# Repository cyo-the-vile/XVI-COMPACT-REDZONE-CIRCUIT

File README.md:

# XVI-COMPACT-REDZONE-CIRCUIT
Simple circuit to overclock XVI Compact

To build this circuit it is recommended you send this board to a manufacturer to make a blank PCB. I prefer JLCPCB.  Both zipped files are what are good to send to a PCB manufacturer.  

The XVI Compact is capable of being clocked up to 24mhz.  After 25mhz the processor will become unstable.

This circuit is based on the one in the Oh! Magazine scans.  Hlide was very nice also also made a circuit with DIP packages.  Anyway this is SMD packaging board so it's smaller.
There are two solder points labeled SW for a switch.
There are 4 solder points labeled for 5V, GND, I AND O.  This is important for soldering wires to the motherboard for overclocking.

Anyway the BOM consists of:

-DIP 14 socket...trim it so it can insert properly. It will fit.  This gives you leverage on what size crystal to use.

-If you want a 24mhz computer you will need a 48mhz oscillator since clock divider is 2.  
For a 20mhz computer you will need 40mhz oscillator. They need to be in DIP package and 5V.

-4.7K OHM resistor specifcally in 0603 SMD package.

-SN74F157AD which is the SOIC16 package.

This will be updated as I build mine and test it live.

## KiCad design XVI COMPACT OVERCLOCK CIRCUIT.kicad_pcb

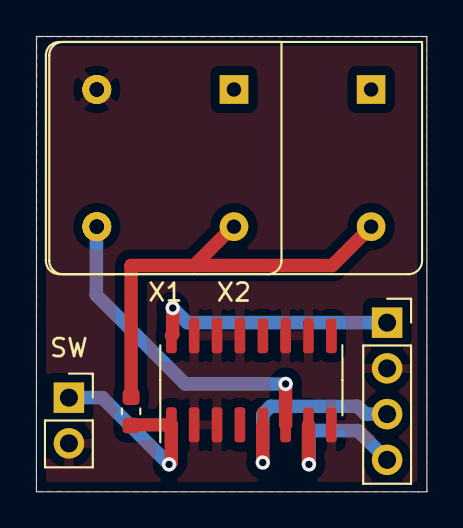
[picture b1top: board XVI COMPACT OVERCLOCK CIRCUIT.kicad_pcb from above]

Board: 2 copper layers, 21.7 x 25.3 mm, 6 parts (0 on the bottom side), 5 nets.

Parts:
J2: Conn_01x04; PinSocket_1x04_P2.54mm_Vertical
R1: 4.7K; R_0603_1608Metric
SW: FOR SWITCH; PinSocket_1x02_P2.54mm_Vertical
U1: SOIC16; SOIC-16_3.9x9.9mm_P1.27mm
X1: CXO_DIP8; Oscillator_DIP-8
X2: CXO_DIP14; Oscillator_DIP-14

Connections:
/GND: J2.2, SW.2, U1.2, U1.3, U1.8, U1.10, U1.11, U1.13, U1.14, U1.15, X1.4, X2.7
/I: J2.3, U1.5
/O: J2.4, U1.7
/VCC: J2.1, R1.1, R1.2, SW.1, U1.1, U1.16, X1.8, X2.14
unnamed: U1.6, X1.5, X2.8
